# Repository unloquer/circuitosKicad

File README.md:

# circuitosKicad
libreria de footprints y componentes, pcb's, esquematicos

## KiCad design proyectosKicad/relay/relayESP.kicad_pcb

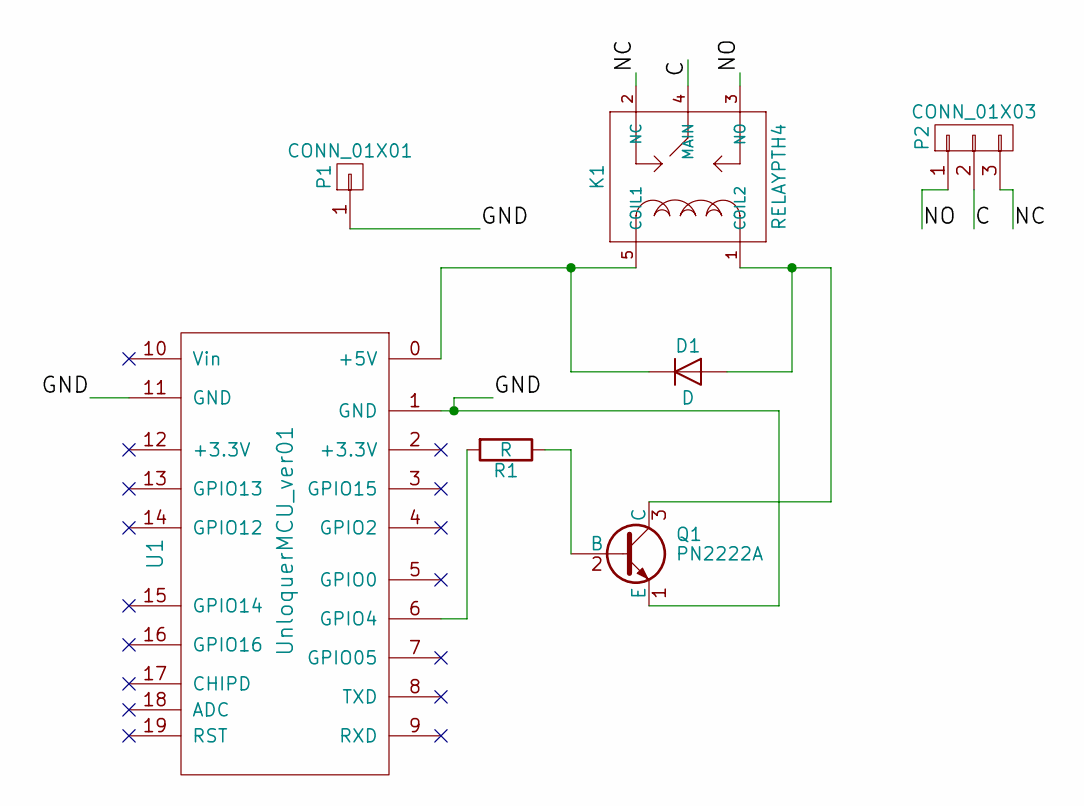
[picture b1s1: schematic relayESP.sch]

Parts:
D1: D; D_5KPW_P7.62mm_Vertical_AnodeUp
K1: RELAYPTH4; Relay_SANYOU_SRD_Series_Form_C_small
P1: CONN_01X01; Pin_Header_Straight_1x01_Pitch2.54mm
P2: CONN_01X03; Pin_Header_Straight_1x03_Pitch2.54mm
Q1: PN2222A; OldSowjetaera_Transistor_Type-II_BigPads
R1: R; R_Axial_DIN0309_L9.0mm_D3.2mm_P12.70mm_Horizontal
U1: UnloquerMCU_ver01; UnloquerMCU_ver01_footprint

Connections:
/C: K1.4 (MAIN), P2.2
/GND: P1.1, Q1.1 (E), U1.1 (GND), U1.11 (GND); also elsewhere on the board
/NC: K1.2 (NC), P2.3
/NO: K1.3 (NO), P2.1
unnamed 4: D1.1 (K), K1.5 (COIL1), U1.0 (+5V); also elsewhere on the board
unnamed: D1.2 (A), K1.1 (COIL2), Q1.3 (C)
unnamed: Q1.2 (B), R1.1
unnamed 7: R1.2, U1.6 (GPIO4); also elsewhere on the board
unnamed 8: U1.2 (+3.3V); also elsewhere on the board
unnamed 9: U1.3 (GPIO15); also elsewhere on the board
unnamed 10: U1.4 (GPIO2); also elsewhere on the board
unnamed 11: U1.5 (GPIO0); also elsewhere on the board
unnamed 12: U1.7 (GPIO05); also elsewhere on the board
unnamed 13: U1.8 (TXD); also elsewhere on the board
unnamed 14: U1.9 (RXD); also elsewhere on the board
unnamed 15: U1.10 (Vin); also elsewhere on the board
unnamed 16: U1.12 (+3.3V); also elsewhere on the board
unnamed 17: U1.13 (GPIO13); also elsewhere on the board
unnamed 18: U1.14 (GPIO12); also elsewhere on the board
unnamed 19: U1.15 (GPIO14); also elsewhere on the board
unnamed 20: U1.16 (GPIO16); also elsewhere on the board
unnamed 21: U1.17 (CHIPD); also elsewhere on the board
unnamed 22: U1.18 (ADC); also elsewhere on the board
unnamed 23: U1.19 (RST); also elsewhere on the board

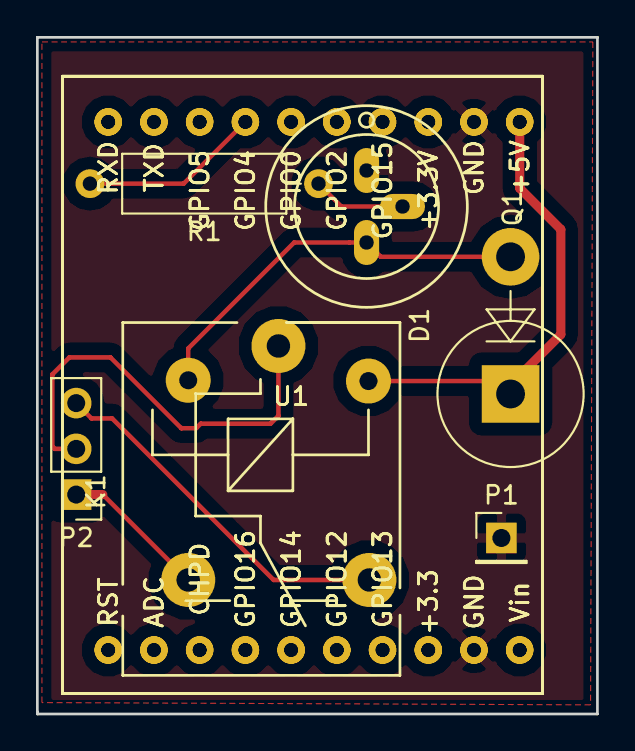
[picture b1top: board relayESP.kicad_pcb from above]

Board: 2 copper layers, 31.1 x 37.6 mm, 8 parts (0 on the bottom side), 24 nets.

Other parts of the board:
U1#2: UnloquerMCU_ver01; UnloquerMCU_ver01_footprint

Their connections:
/GND: U1#2.1, U1#2.11; also elsewhere on the board
unnamed 4: U1#2.0; also elsewhere on the board
unnamed 7: U1#2.6; also elsewhere on the board
unnamed 8: U1#2.2; also elsewhere on the board
unnamed 9: U1#2.3; also elsewhere on the board
unnamed 10: U1#2.4; also elsewhere on the board
unnamed 11: U1#2.5; also elsewhere on the board
unnamed 12: U1#2.7; also elsewhere on the board
unnamed 13: U1#2.8; also elsewhere on the board
unnamed 14: U1#2.9; also elsewhere on the board
unnamed 15: U1#2.10; also elsewhere on the board
unnamed 16: U1#2.12; also elsewhere on the board
unnamed 17: U1#2.13; also elsewhere on the board
unnamed 18: U1#2.14; also elsewhere on the board
unnamed 19: U1#2.15; also elsewhere on the board
unnamed 20: U1#2.16; also elsewhere on the board
unnamed 21: U1#2.17; also elsewhere on the board
unnamed 22: U1#2.18; also elsewhere on the board
unnamed 23: U1#2.19; also elsewhere on the board

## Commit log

2017-02-25 footprints de relay y primera version del modulo esp, pcb modulo relay
2017-04-18 agregados proyectos de modulo relay y modulo calidad aire, revisar los path relativos a los footprints y componentes a medida
2017-04-18 componente esp version 1
2017-04-24 ruteada tarjeta calidad aire, revisar footprint capacitor, muy pequeno
2017-04-24 path relativos agregados al proyecto
2017-05-01 footprint de transistor mas grande
2017-05-13 version sensor plantTower
2017-05-15 alimentacion y pines ok
